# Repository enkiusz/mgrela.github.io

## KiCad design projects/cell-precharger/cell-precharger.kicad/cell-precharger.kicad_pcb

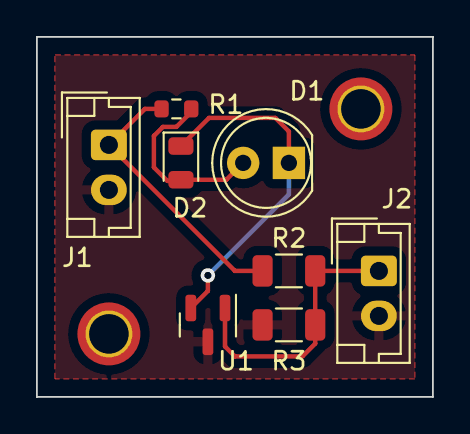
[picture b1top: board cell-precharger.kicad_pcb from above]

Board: 2 copper layers, 22.0 x 20.0 mm, 8 parts (0 on the bottom side), 5 nets.

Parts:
D1: LED; LED_D5.0mm
D2: LED; LED_0805_2012Metric
J1: Vin; JST_EH_B2B-EH-A_1x02_P2.50mm_Vertical
J2: Vbat; JST_EH_B2B-EH-A_1x02_P2.50mm_Vertical
R1: 100; R_0603_1608Metric
R2: 100 / 0.25W / 1%; R_1206_3216Metric
R3: 110 / 0.25W / 1%; R_1206_3216Metric
U1: CJ431; SOT-23

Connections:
+5V: J1.1, R1.1, R2.1
GND: J1.2, J2.2, R3.2, U1.3 (A)
unnamed: D1.1 (K), D2.1 (K), U1.2 (K)
unnamed: D1.2 (A), D2.2 (A), R1.2
unnamed: J2.1, R2.2, R3.1, U1.1 (REF)

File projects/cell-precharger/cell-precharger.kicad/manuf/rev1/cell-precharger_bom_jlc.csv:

"Comment","Designator","Footprint","LCSC Part #"
"100","R1","R_0603_1608Metric","C22775"
"100 / 1%","R2","R_1206_3216Metric","C17901"
"110 / 1%","R3","R_1206_3216Metric","C17905"
"CJ431","U1","SOT-23","C3113"

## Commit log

2021-04-11 Configure CNAME and hooks
2021-04-11 githooks: Don't run exiv2 when no images are found
2021-04-11 rebuild
2021-05-13 githooks: Keep orientation
2022-11-06 remove spurious kicad files
